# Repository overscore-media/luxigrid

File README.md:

# Luxigrid

Luxigrid is a WiFi-enabled LED matrix for your desk, compatible with an ecosystem of 25+ apps and counting.

The hardware and software are open-source, so you can build one yourself. Or buy one pre-assembled or as a kit from [our website](https://luxigrid.overscore.media)!

## Quick Specs

- 2048 RGB LEDs (in 64x32 grid)
- Browser-Based Web Interface
  - Configure important settings (WiFi, time/date, browse files on SD card, etc.)
  - Upload new apps over WiFi
  - Modify app-specific settings
- Can connect to the Internet (for stocks/weather/news/other info)
- Automatically adjusts its brightness (integrated light sensor)
- Temperature/Humidity Sensor (for an indoor weather station)
- Buzzer for playing alarms, alerts, and chiptunes
- Automatically adjusts for daylight savings time
- Keeps time even when the power goes out (real-time clock on-board)
- Made with readily-available components
- Open-Source
  - Build your own, or modify the code/hardware files to your heart's content
  - Code available under the MIT License
  - 3D printed parts available under the CC-BY-4.0 license
  - PCB Gerbers and KiCad project available and free to use as you see fit

## Quick Start Guide

If you're looking for help setting up your Luxigrid, we've assembled a Quick Start Guide with answers to your most common questions and troubleshooting help.

View the latest version of the [Quick Start Guide](./QUICK_START_GUIDE.md).

For technical support, you can also contact us on [our website](https://luxigrid.overscore.media). Please note that we only provide official support for products purchased from our website. But we'd be happy to chat with you, regardless of whether you've purchased a Luxigrid from our website, or built your own from scratch.

## Technical Details

- 64x32 LED matrix with 4mm pitch
  - Total of 2048 RGB LEDs
  - Compatible with HUB75 protocol
  - Readily available on sites like Aliexpress

- ESP32-DevKitC V4 board
  - ESP32-WROOM-32D processor module
  - WiFi (b/g/n 2.4 GHz) and Bluetooth 4.2
  - 240 MHz Clock Speed
  - 520 KB SRAM (16 KB cache) and 448 KB ROM
  - 1.75 MB of usable flash memory (with OTA updates enabled)
  - Readily available on many sites for under $10
  - Reference: <https://docs.espressif.com/projects/esp-idf/en/stable/esp32/hw-reference/esp32/get-started-devkitc.html>

- Custom PCB
  - Micro SD card reader
  - BME680 Environmental Sensor (temperature, humidity, air pressure)
  - BH1750 Light Sensor (for automatic screen brightness)
  - DS3231 Real-Time Clock (powered by a CR2032 coin cell battery)
  - Piezo Passive Buzzer
  - On/Off Rocker Switch
  - 2.5mm DC Barrel Jack for power

- Power Consumption: 5V DC - 3+ Amps at peak
  - *Please use a power supply capable of delivering at least 4A*

## Assembly Instructions

The process of assembling your own Luxigrid is fairly intensive, but should be documented well enough to be a fair challenge. If you're building one from scratch, you'll need to have purchased the parts from the Bill of Materials, have access to a 3D Printer, and be comfortable with soldering. It's not too difficult, as far as these sorts of electronics projects go, but it may not be for the faint of heart.

[View the full assembly instructions](./ASSEMBLY.md).

Alternatively, you can purchase a Luxigrid in kit form or pre-assembled from [our website](https://luxigrid.overscore.media).

## Development Instructions

The Luxigrid software is split into two semi-distinct components - the C++ firmware that resides on the ESP32, and the HTML/CSS/JavaScript-based web interface that runs on your browser. Since the ESP32 also acts as a web server, there is a level of integration involved. But the most complicated part of the software is its ability to support an arbitrary number of apps. Only one app can be installed on a Luxigrid at a time, and each app must be compiled separately (with its own firmware and web interface). But apps can be swapped between on the fly, thanks to the ESP32's Over-The-Air (OTA) update capability.

Needless to say, the underlying setup to make all of this work is pretty complex. And there are still potential areas for improvement. But we've done what we can to document the process.

[View the full development instructions](./DEVELOPING.md).

Alternatively, you can download the latest compiled versions of the available apps from the official [Luxigrid App Store](https://luxigrid.overscore.media/apps), or the [GitHub Releases page](https://github.com/overscore-media/luxigrid/releases).

## Found an Issue?

Let us know by [creating an Issue](https://github.com/overscore-media/luxigrid/issues) on this GitHub repository. Or if you have a bugfix, feature, or new application you'd like to share, feel free to open a [Pull Request](https://github.com/overscore-media/luxigrid/pulls). We also welcome GitHub stars, forks, and watchers.

For answers to specific questions, or if you just want to chat, drop us a line at [luxigrid.overscore.media](https://luxigrid.overscore.media).

## Credits

OverScore Media wishes to recognize the many giants whose shoulders this project stands upon. Thank you for your contributions to creativity and technology. We hope this project serves as an inspiration to others, like so many have been inspirations to us.

This includes the following individuals and teams. If we've missed any, please let us know. But be assured that their contributions have not gone unappreciated.

Where appropriate, additional copyright notices and software licenses have also been placed in the code. See also [licenses/credits.md](./licenses/credits.md).

### Software Libraries

- [ESP32 HUB75 LED Matrix Panel DMA Display](https://github.com/mrcodetastic/ESP32-HUB75-MatrixPanel-DMA) by @mrcodetastic on GitHub
- [Adafruit GFX Library](https://github.com/adafruit/Adafruit-GFX-Library)
- [Adafruit BusIO](https://github.com/adafruit/Adafruit_BusIO)
- [Adafruit Unified Sensor](https://github.com/adafruit/Adafruit_Sensor)
- [Adafruit BME680 Library](https://github.com/adafruit/Adafruit_BME680)
- [Adafruit RTClib](https://github.com/adafruit/RTClib)
- [BH1750](https://github.com/claws/BH1750) by @claws on GitHub
- [ESP Async WebServer](https://github.com/mathieucarbou/ESPAsyncWebServer) originally by [@me-no-dev](https://github.com/me-no-dev/ESPAsyncWebServer), then forked by [@yubox-node-org](https://github.com/yubox-node-org/ESPAsyncWebServer), then forked by [@mathieucarbou](https://github.com/mathieucarbou)
- [ArduinoJson](https://arduinojson.org/)
- [AnimatedGIF](https://github.com/bitbank2/AnimatedGIF) by @bitbank2
- [FastLED](https://github.com/FastLED/FastLED)

### Projects

The following projects have served as direct inspiration for parts of the Luxigrid firmware.

- [myClock](https://github.com/dragondaud/myClock) by @dragondaud on GitHub
- [Pong Wars for M5Stack](https://github.com/anoken/pong-wars-forM5Stack) by @anoken on GitHub
- [PONG clock](https://github.com/conejoninja/pongclock/) by @conejoninja on GitHub
- [Aurora](https://github.com/pixelmatix/aurora) by Jason Coon
- [minimalUploadAuthESP32](https://github.com/CelliesProjects/minimalUploadAuthESP32/blob/master/minimalUploadAuthESP32.ino) by @CelliesProjects on GitHub

### Development Tools

- [Arduino](https://www.arduino.cc/)
- [ESP32](https://www.espressif.com/en/products/socs/esp32)
- [PlatformIO](https://platformio.org/)
- [Visual Studio Code](https://code.visualstudio.com/)

### Web Development Tools

- [Tailwind.css](https://tailwindcss.com/)
- [Vite](https://vitejs.dev/)
- [JSDOM](https://github.com/jsdom/jsdom)
- [ESLint](https://eslint.org/)
- [ESLint Config XO](https://github.com/xojs/xo)
- [PostCSS](https://postcss.org/)
- [vite-plugin-html](https://github.com/vbenjs/vite-plugin-html)
- [vite-plugin-singlefile](https://github.com/richardtallent/vite-plugin-singlefile)
- [CSSNano](https://github.com/cssnano/cssnano)
- [Iconoir](https://iconoir.com/)

### Data Sources

- [Open-Meteo](https://open-meteo.com/) (for weather data)
- [Finnhub Stock API](https://finnhub.io/) (for stock data)
- [Wikipedia](https://www.wikipedia.org/) (for periodic table of elements data)
- <https://github.com/nayarsystems/posix_tz_db> (for timezone data)

### 3D Software

That's right. Luxigrid's 3D-printed parts were designed with free and open-source software!

- [FreeCAD](https://www.freecad.org/)
- [OpenSCAD](https://openscad.org/)
- [PrusaSlicer](https://www.prusa3d.com/page/prusaslicer_424/)

### 3D Models

This excellent 3D model was used as the basis for the desk mount. Our modified version is a bit taller, and uses an M4 bolt instead of an M5.

- [Vesa 75x75 monitor stand](https://www.thingiverse.com/thing:3808242) by @choosecool on Thingiverse
  - Licensed under the [Creative Commons - Attribution license](https://creativecommons.org/licenses/by/4.0/).

### Tutorials

These helpful tutorial creators have served as invaluable references during various parts of the concept, design, and production phases of this project. Thanks for sharing your knowledge!

- [Random Nerd Tutorials](https://randomnerdtutorials.com/) for a wealth of electronics tutorials
- [@Swiss_Cheese on YouTube](https://www.youtube.com/@Swiss_Cheese.) for PrusaSlicer tips and tricks
- [@ontherundesign's Hirth Joint](https://www.thingiverse.com/thing:2937436) FreeCAD Tutorial
- [RGB Panel Hookup Guide](https://learn.sparkfun.com/tutorials/rgb-panel-hookup-guide) by Sparkfun
- [Adafruit GFX Library Guide](https://cdn-learn.adafruit.com/downloads/pdf/adafruit-gfx-graphics-library.pdf) by Phillip Burgess

### Inspirations

These are some of the hardware projects and commercial products that have served as indirect inspirations for the development of Luxigrid. There were times when it seemed impractical to complete, but the existence of these projects gave us hope that it could be done. Hopefully this project can serve as such an inspiration to others. Your dreams may not be so unachievable, after all! :)

- [Tidbyt](https://tidbyt.com/)
- [Clockwise](https://clockwise.page/)
- [Adafruit Matrix Portal](https://www.adafruit.com/product/4745)
- [Pico RGB Matrix P3 64x32](https://www.waveshare.com/wiki/Pico-RGB-Matrix-P3-64x32) by Waveshare
- [Pixel Art Matrix Display](https://www.printables.com/model/600039-pixel-art-matrix-display) by @Till_312394 on Printables
- [Pixel Art with 64 LED Matrix WS2812B - v2](https://www.printables.com/model/946221-pixel-art-with-64-led-matrix-ws2812b-v2-new-led-di) by @Regis on Printables
- [ESP32 HUB75 LED Matrix Driver](https://github.com/rorosaurus/esp32-hub75-driver) by @rorosaurus on GitHub
- [ESP32 I2S Matrix Shield](https://www.tindie.com/products/brianlough/esp32-i2s-matrix-shield/) by Brian Lough
- [ESP32 D1 Mini D1 RGB Matrix Shield](https://github.com/hallard/WeMos-Matrix-Shield-DMA) by @hallard on GitHub
- [ESP Pixel Matrix](https://github.com/hanneslinder/esp-pixel-matrix) by @hanneslinder on GitHub
- [PxMatrix](https://github.com/2dom/PxMatrix) by @2dom on GitHub
- [HUB75 Pixel Art Display](https://github.com/mzashh/HUB75-Pixel-Art-Display) by @mzashh on GitHub
- [RGB Matrix Panel Shield for ESP32](https://www.tindie.com/products/lightwell/rgb-matrix-panel-shield-for-esp32/) by LIGHTWELL
- [ESP8266 RGB Matrix Cable Version](https://github.com/mike-rankin/ESP8266_RGB_Matrix_Cable_Version) by Mike Rankin

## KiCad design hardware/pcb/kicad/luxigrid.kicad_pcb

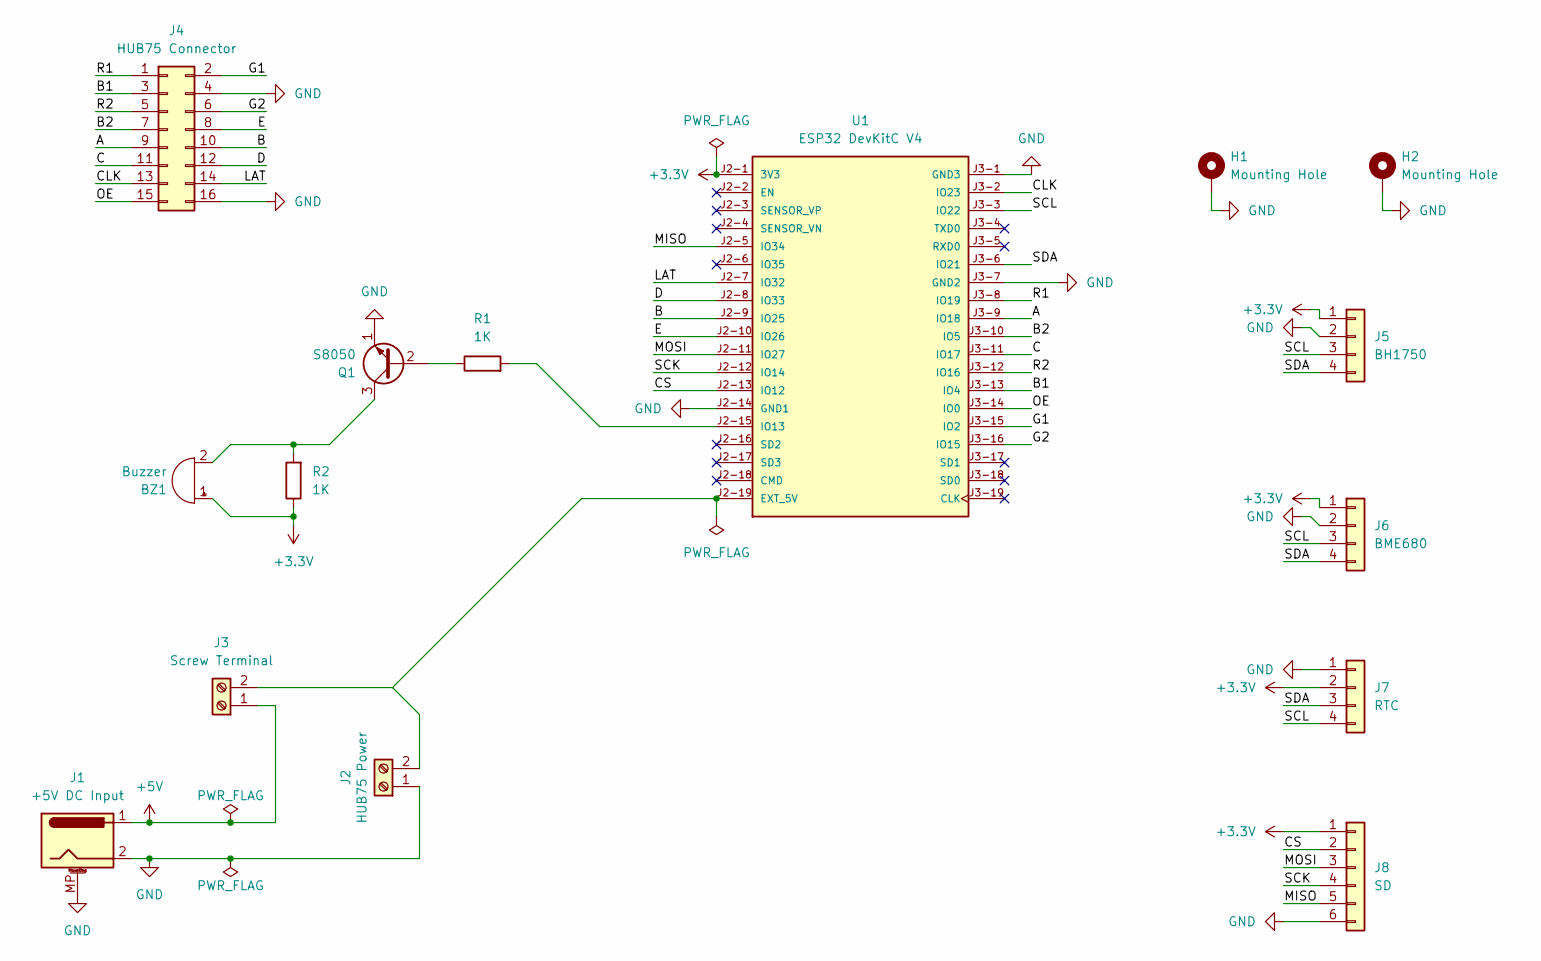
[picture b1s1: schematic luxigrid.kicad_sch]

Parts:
BZ1: Buzzer; Buzzer_TDK_PS1240P02BT_D12.2mm_H6.5mm
H1, H2: Mounting Hole; MountingHole_3.2mm_M3_ISO14580_Pad
J1: +5V DC Input; BarrelJack_Horizontal
J2: HUB75 Power; 7.62mm Barrier Block
J3: Screw Terminal; 5mm Screw Terminal Block
J4: HUB75 Connector; PinSocket_2x08_P2.54mm_Vertical
J5: BH1750; PinSocket_1x04_P2.54mm_Vertical
J6: BME680; PinSocket_1x04_P2.54mm_Vertical
J7: RTC; PinSocket_1x04_P2.54mm_Vertical
J8: SD; PinSocket_1x06_P2.54mm_Vertical
Q1: S8050; SS8050DTA Transistor
R1, R2: 1K; R_Axial_DIN0309_L9.0mm_D3.2mm_P15.24mm_Horizontal
U1: ESP32 DevKitC V4; PARTREV V4

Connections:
+3.3V: BZ1.1 (+), J5.1, J6.1, J7.2, J8.1, R2.1, U1.J2-1 (3V3)
+5V: J1.1, J3.1
/A: J4.9, U1.J3-9 (IO18)
/B: J4.10, U1.J2-9 (IO25)
/B1: J4.3, U1.J3-13 (IO4)
/B2: J4.7, U1.J3-10 (IO5)
/C: J4.11, U1.J3-11 (IO17)
/CLK: J4.13, U1.J3-2 (IO23)
/CS: J8.2, U1.J2-13 (IO12)
/D: J4.12, U1.J2-8 (IO33)
/E: J4.8, U1.J2-10 (IO26)
/G1: J4.2, U1.J3-15 (IO2)
/G2: J4.6, U1.J3-16 (IO15)
/LAT: J4.14, U1.J2-7 (IO32)
/MISO: J8.5, U1.J2-5 (IO34)
/MOSI: J8.3, U1.J2-11 (IO27)
/OE: J4.15, U1.J3-14 (IO0)
/R1: J4.1, U1.J3-8 (IO19)
/R2: J4.5, U1.J3-12 (IO16)
/SCK: J8.4, U1.J2-12 (IO14)
/SCL: J5.3, J6.3, J7.4, U1.J3-3 (IO22)
/SDA: J5.4, J6.4, J7.3, U1.J3-6 (IO21)
GND: H1.1, H2.1, J1.2, J1.MP (MountPin), J2.1, J4.4, J4.16, J5.2, J6.2, J7.1, J8.6, Q1.1 (E), U1.J2-14 (GND1), U1.J3-1 (GND3), U1.J3-7 (GND2)
unnamed: BZ1.2 (-), Q1.3 (C), R2.2
unnamed: J2.2, J3.2, U1.J2-19 (EXT_5V)
unnamed: Q1.2 (B), R1.1
unnamed: R1.2, U1.J2-15 (IO13)

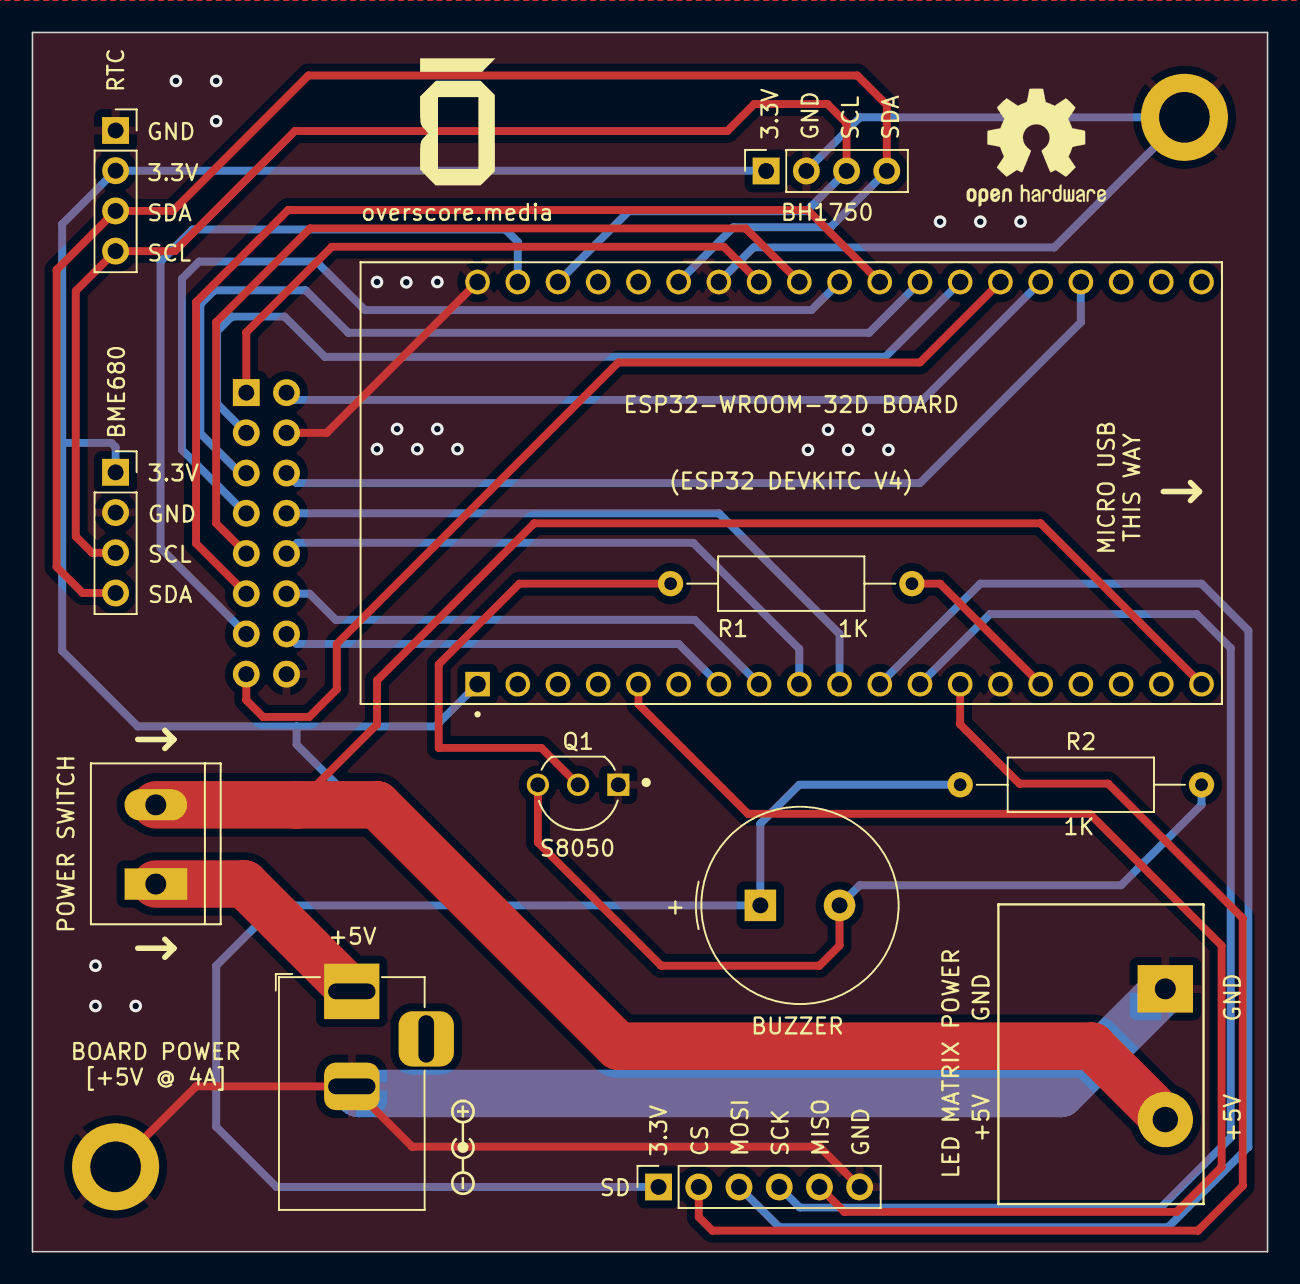
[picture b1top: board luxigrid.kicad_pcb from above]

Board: 2 copper layers, 78.0 x 77.0 mm, 15 parts (1 on the bottom side), 27 nets.

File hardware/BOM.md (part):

# Luxigrid - Bill of Materials

This is the list of the parts/tools you may need to assemble a Luxigrid of your own. Fair warning, it's a fairly long list. But we've gone to considerable lengths to ensure the availability/reasonable price of these components. Hopefully they're still relatively easy to find, if and when you choose to embark on this adventure.

You can also purchase a Luxigrid in kit form or pre-assembled from [our website](https://luxigrid.overscore.media) 😉.

**Please Note:** OverScore Media does not guarantee that any of this information is accurate or up-to-date. It is provided for informational purposes only, in the hope that it will be useful. Any images are for illustration only. If you choose to follow these instructions, you do so at your own risk. This is just to let you know what you might be in for. Please be careful.

We've also provided a handy [Shopping List](./luxigrid_shopping_list.xlsx) spreadsheet that you may find helpful.

## Modules

- **LED Matrix**
  - P4 64x32 LED Matrix
  - 256x128mm
  - HUB75
  - Your mileage may vary, but Muen LED/MuenShop on Aliexpress has good deals
  - *Must be compatible with the ESP32 HUB75 MatrixPanel DMA Library* - see <https://github.com/mrcodetastic/ESP32-HUB75-MatrixPanel-DMA?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

- **ESP32-DevKitC V4 Board**
  - You're looking for a **38-pin** ESP32 board that has an **ESP32-WROOM-32D** chip and **Micro USB**
  - Look for the one that matches this picture *exactly*, since the Luxigrid PCB is built around it
  - They shouldn't be too hard to find, if you know what you're looking for - i.e., this:

![38-pin Microcontroller board powered by ESP32-WROOM-32D chip](../docs/images/esp32_devkitc_v4.jpg)

- **DS3231 RTC Module**
  - These RTC modules are fairly easy to find
  - Some come with a battery included, but you're probably better off finding a battery elsewhere (more on that below)
  - Note: To install it on the Luxigrid PCB, you'll need to solder 4 male header pins facing downwards (as shown in the picture)
  - Many modules come with 4 extra male header pins for this purpose
  - Also, don't mind the subpar soldering job on this and other parts. These were from an early test - we've had more practice since then.

![Front of RTC Module, with CR2032 Battery, 4 pins on left side, and 6 pins on right side](../docs/images/rtc_front.jpg)
![Backside of RTC Module, 6 pins on left side pointing sideways, and 4 pins on right side pointing up](../docs/images/rtc_back.jpg)

- **BME680 Module**
  - Unfortunately, this module can be quite pricey, as the sensor itself is about $4 CAD. Try to find one under $10 CAD, if possible.
  - Granted, *good luck* finding anywhere near as accurate/powerful a sensor for the price point that can do temperature and humidity.
  - It must have VCC, GND, SCL, SDA, SDO, and CS pins as shown. Although Luxigrid doesn't use the SDO and CS pins; just the other pins for the I2C interface
  - For whatever reason, these are usually purple. But you might find one in black or other colour. As long as it has the same board shape and pinout, you should be fine.
  - You will need to solder a 6-pin (or at least a 4-pin; SDO and CS are unused) male header to the pins as shown, with the "back" side of the board facing up. The orientation is very important.

![Front of BME680 module, with 6 header pins sticking up on the left, and the sensor itself on a protrustion of the purple PCB to the right](../docs/images/bme680_front.jpg)
![Bottom of BME680 module, with 6 header pins facing dowards on the right](../docs/images/bme680_back.jpg)

- **Micro SD Card Module - 3.3V Logic**
  - This is unfortunately one of the trickier ones to find - not because there aren't many out there, but because there are many incompatible products that look similar.
  - This module you want is very small, and it runs off **3.3V logic**. Many Arduino-compatible SD card modules use 5V logic
  - You can generally tell them apart, because the 5V ones are a bit bigger, and they have a little black part with three "legs" and a "hat" - that's the voltage regulator. You don't want one of them.
  - "Mini TF Card Module" might help in your search
  - Try not to get dinged on shipping, but these shouldn't be more than about $1.50 CAD.
  - You're going to want to solder 6 male header pins (often included) facing up from the top
  - So if you put the module on its back (the side without the micro SD card slot) the pins should be pointing down

![Front of Micro SD Card Module, with 4 small resistors and 2 capacitors beside the Micro SD card slot, and 6 male header pins facing upwards](../docs/images/microsd_module_front.jpg)

![Bottom of Micro SD Card Module, with 6 male header pins facing downwards](../docs/images/microsd_module_back.jpg)

- **BH1750 Module**
  - These are readily available, often under the name "GY-302"
  - It's a rectangular board with a BH1750 chip, five pins, and two screw holes
  - You'll need to solder 5 male header pins facing away from the front, where the sensor is (or at least 4; the ADDR pin is unused by Luxigrid)
  - The little black rectangle on the front-middle of the board is the sensor itself

![Front of BH1750 Module, with two screw holes on one side and five male header pins facing down on the other side. In the middle is a small black rectangle and the text BH1750](../docs/images/bh1750_front.jpg)
![Back of the BH1750 Module, called GY-302. Five male header pins are sticking upwards](../docs/images/bh1750_back.jpg)

## Passive Components

- **Resistors - 1K** - x2
  - You'll need two 1K (that's one Kiloohm) resistors for hooking up the buzzer
  - The main requirements are the 1K resistance and that they're through-hole components
  - Resistors are generally a pretty generic part, but these were the ones we found. Anything similar to these is probably going to work: [MFR50SFTE52-1K](https://www.mouser.ca/ProductDetail/603-MFR50SFTE52-1K)

![A group of blue 1K resistors with silver leads and colour bands signifying their resistance level](../docs/images/resistors.jpg)

- **Transistor - S8050** - x1
  - You're looking for an NPN transistor with a through-hole footprint
  - There are many good options out there, but we found these ones work really well. The ones with "kinked leads" make soldering them a bit easier: [SS8050DTA](https://www.mouser.ca/ProductDetail/512-SS8050DTA)
  - It doesn't necessarily have to be an S8050, but that part is known to work

![A group of S8050 transistors on a strip of tape, with bent legs to allow for easier soldering](../docs/images/transistors.jpg)

- **Passive Piezo Buzzer** - x1
  - These are a pretty generic part, but you definitely want a **passive** buzzer, not an active buzzer
  - Generally the passive ones have a little green circuit board on the bottom
  - You may have to slightly bend the legs to make it fit the PCB, but that should be fine if you're careful

![Two passive piezo buzzers, showing a plus side on one side, and a green circuit board on the back](../docs/images/passive_buzzers.jpg)

- **DC-Rated Miniature Rocker Switch** - x1
  - These were a royal pain to find, but they're a perfect fit: [Wurth 471002268143](https://www.digikey.ca/en/products/detail/w%C3%BCrth-elektro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
  - You may also have success with the sister model, the [Wurth 471002268142](https://www.digikey.ca/en/products/detail/w%C3%BCrth-elektro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, which just has a different off symbol.
  - These are fairly expensive, at ~$5 CAD per switch, but they are actually rated for DC current. The majority of miniature rocker switches are only rated for AC, and there's no formula to calculate a safe DC rating for an AC switch.
  - If you decide on a different switch, you may have to adjust the 3D model of the left backplane of the Luxigrid enclosure to fit it. But we would strongly recommend not going with a switch that has not been rated for at least 10A DC. For reference, Luxigrid operates at 5V DC, and may draw upwards of 3A when the screen is fully lit.

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
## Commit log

2024-10-19 add script to build all apps, improve documentation
2024-10-19 fix scripts/build_all_apps.py
2025-05-26 expanded flash space, chunked firmware upload with progress indicator, various bug fixes
2025-05-26 fix compilation issues related to networking and ota variables
